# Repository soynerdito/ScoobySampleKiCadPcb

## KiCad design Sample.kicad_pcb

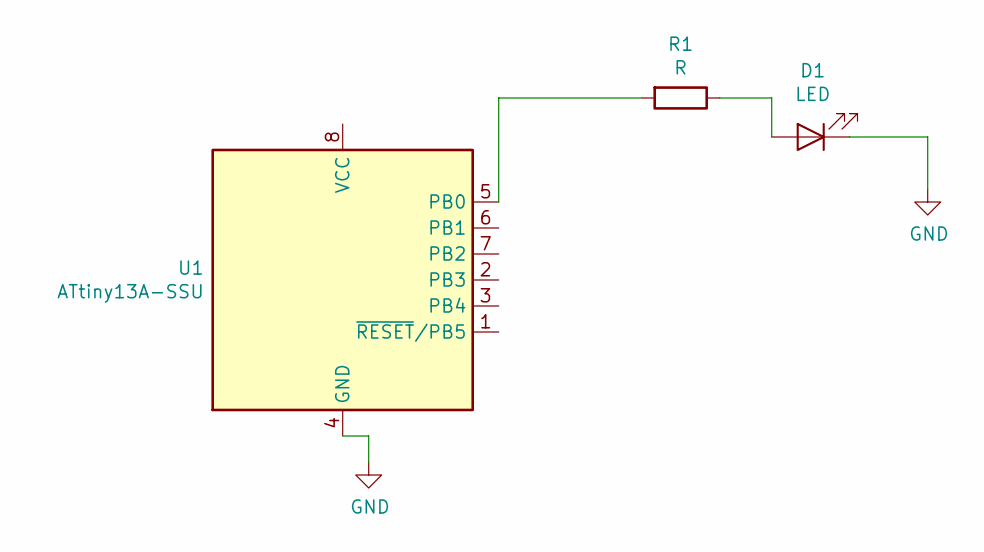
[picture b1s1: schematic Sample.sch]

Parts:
D1: LED; LED_0603_HandSoldering
R1: R; R0603
U1: ATtiny13A-SSU; SOIC8-1.27-5X4MM

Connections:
GND: D1.1 (K), U1.4 (GND)
unnamed: D1.2 (A), R1.1
unnamed: R1.2, U1.5 (PB0)

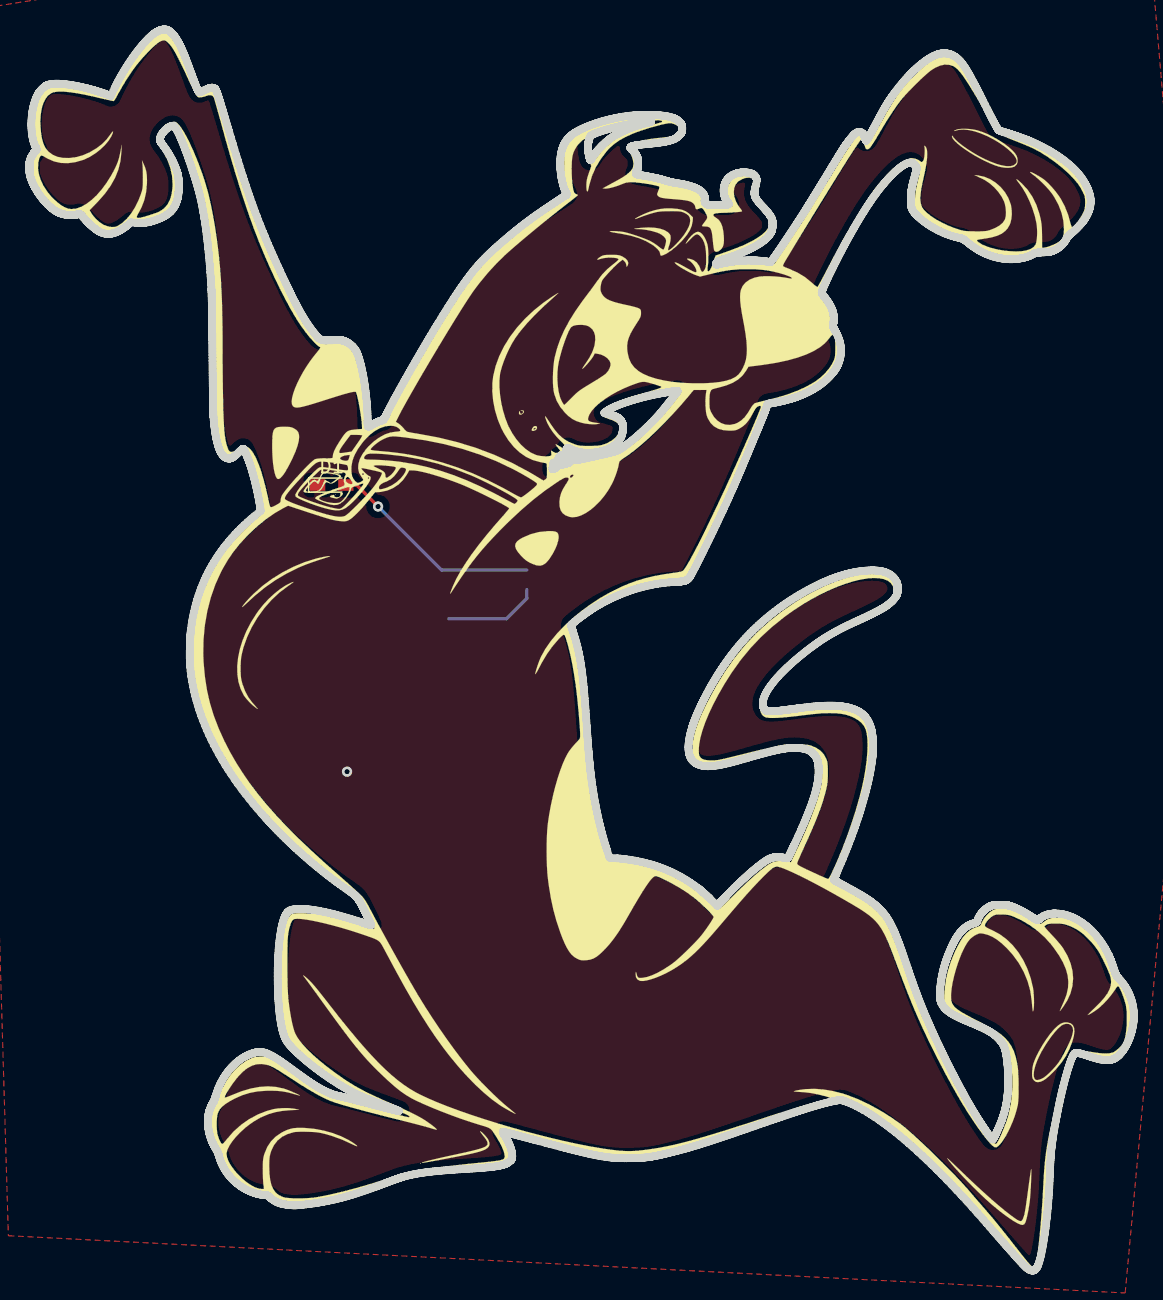
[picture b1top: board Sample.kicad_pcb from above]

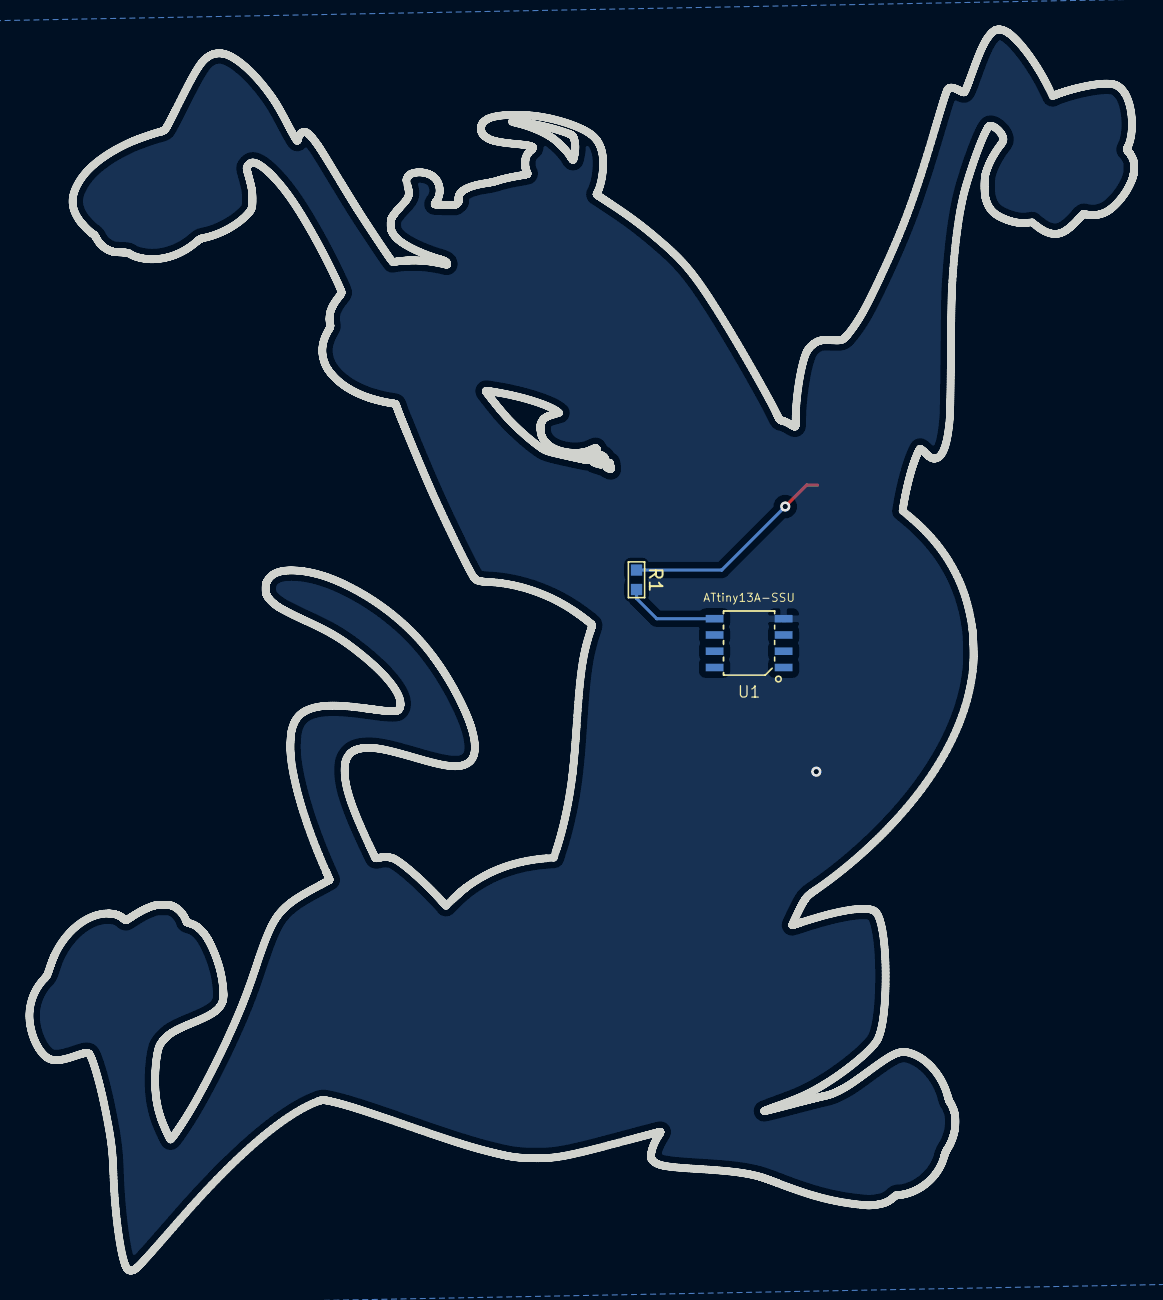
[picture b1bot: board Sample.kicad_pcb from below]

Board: 2 copper layers, 86.3 x 97.0 mm, 3 parts (2 on the bottom side), 3 nets.

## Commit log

2019-07-09 Adding gitignore
2019-07-09 Applying gitignore
